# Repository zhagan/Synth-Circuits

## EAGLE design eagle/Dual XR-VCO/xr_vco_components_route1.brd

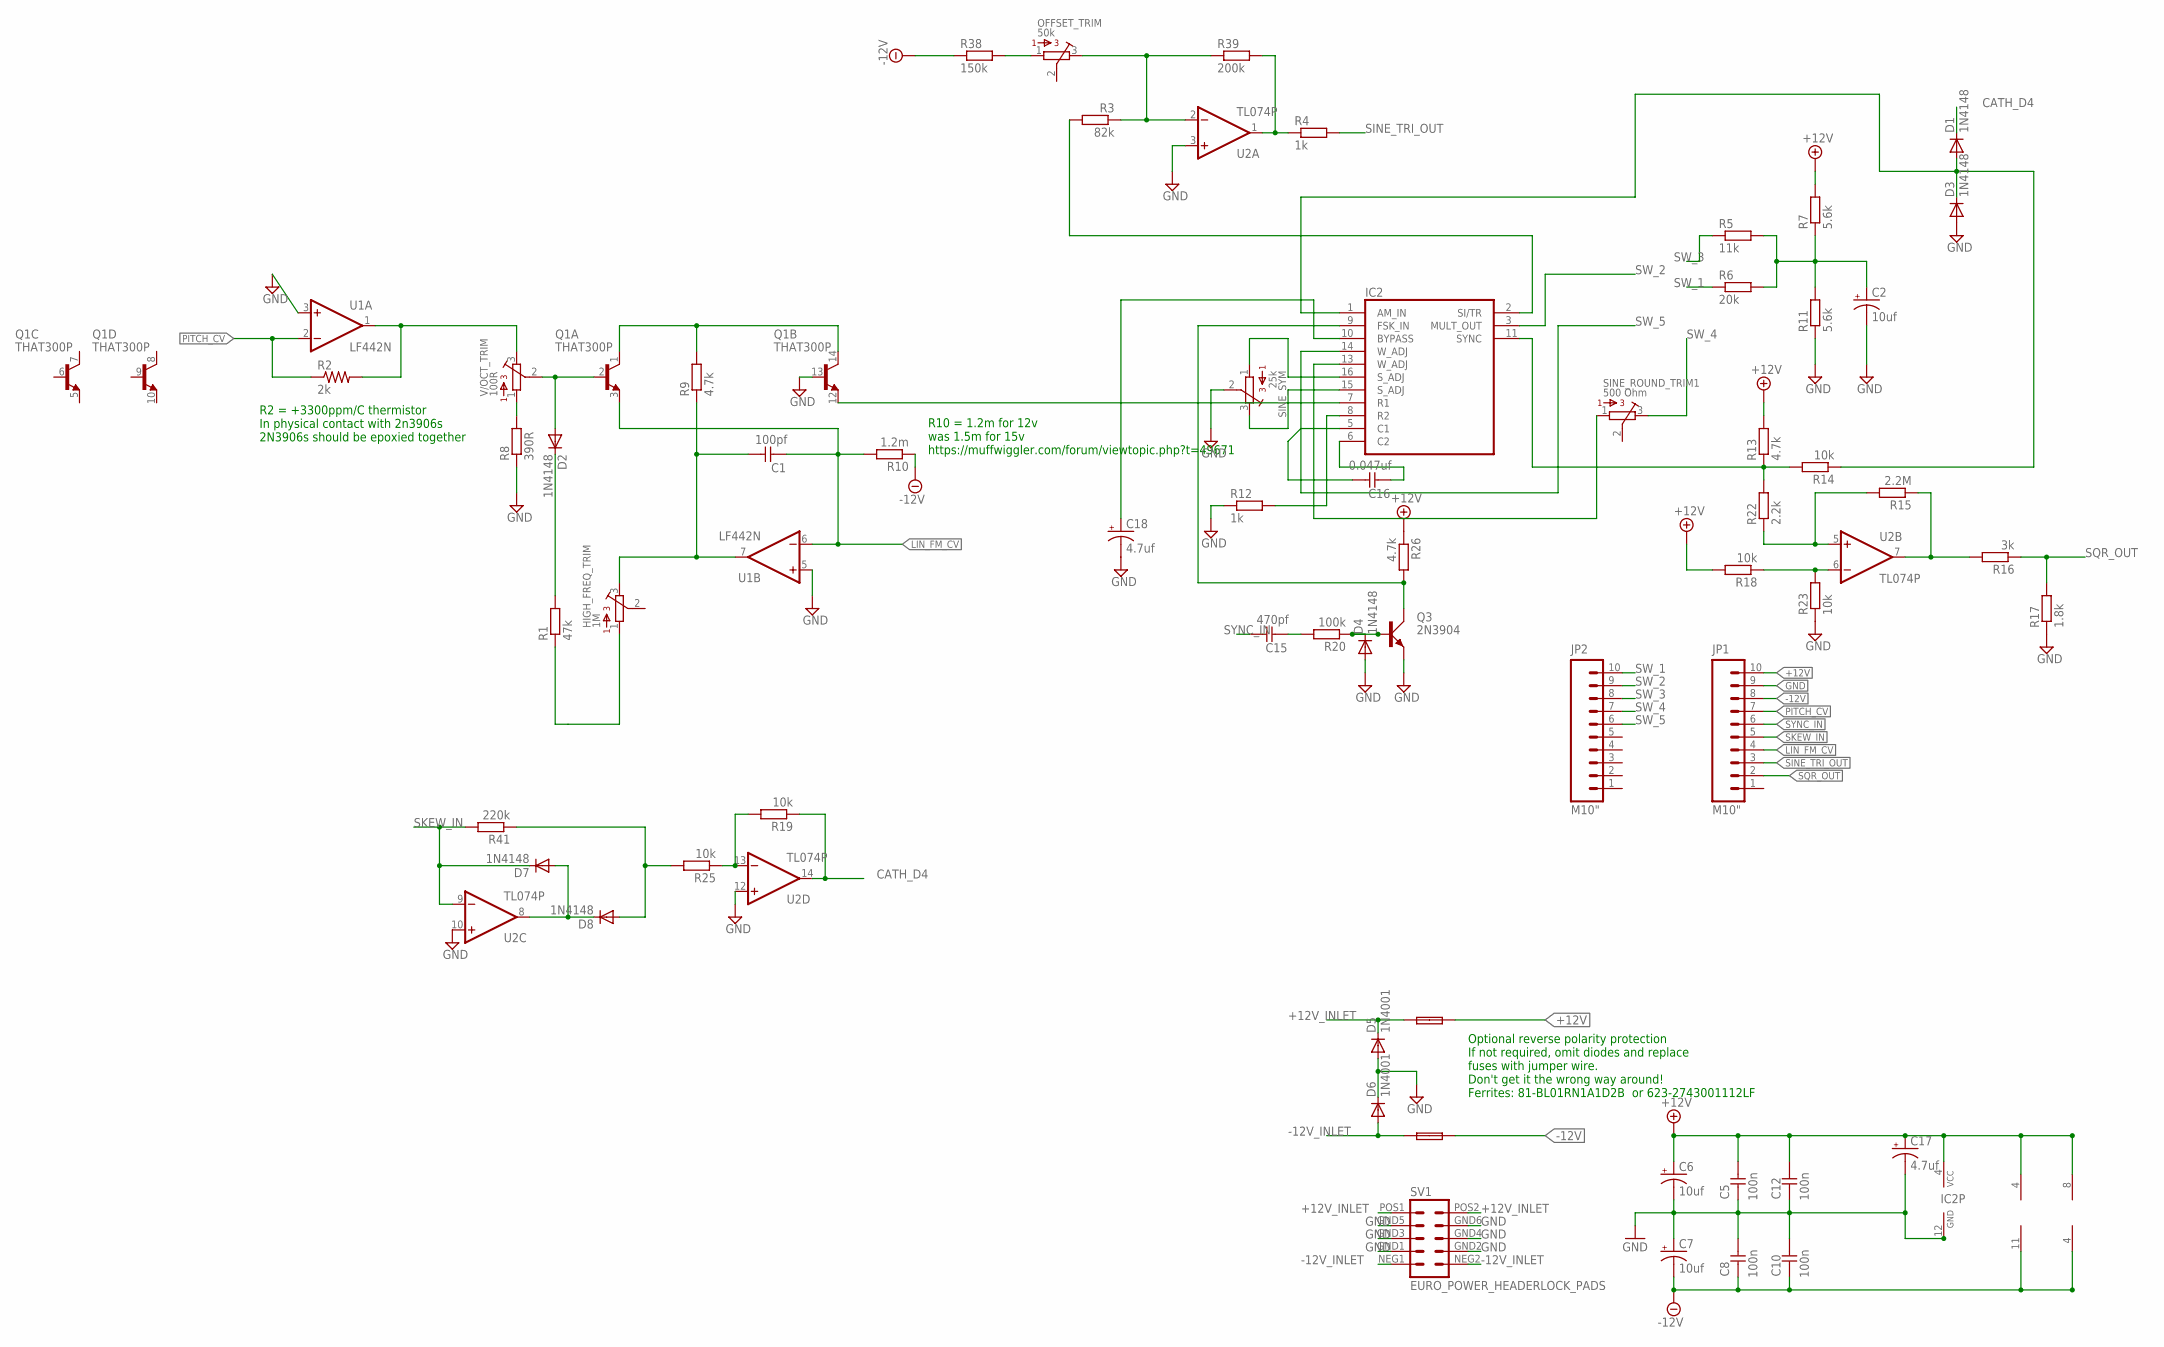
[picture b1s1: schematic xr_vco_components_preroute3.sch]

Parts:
C1: 100pf; C050-024X044
C2, C6, C7: 10uf; CPOL-RADIAL-10UF-25V
C5, C8, C10, C12: 100n; C050-024X044
C15: 470pf; C050-024X044
C16: 0.047uf; C050-024X044
C17, C18: 4.7uf; CPOL-RADIAL-10UF-25V
D1, D2, D3, D4, D7, D8: 1N4148; DO35-7
D5, D6: 1N4001; DO41-10
F1, F2: FUSE; C050H075X075
HIGH_FREQ_TRIM: 1M; BOURNS_3362P_TRIMMER
IC2: XR-2206; DIL16
JP1, JP2: M10"; 1X10
OFFSET_TRIM: 50k; BOURNS_3362P_TRIMMER
Q1: THAT300P; DIL14
Q3: 2N3904; TO92D
R1: 47k; 7MM_RESISTOR
R2: 2k; 0309/12
R3: 82k; 7MM_RESISTOR
R4, R12: 1k; 7MM_RESISTOR
R5: 11k; 7MM_RESISTOR
R6: 20k; 7MM_RESISTOR
R7, R11: 5.6k; 7MM_RESISTOR
R8: 390R; 7MM_RESISTOR
R9, R13, R26: 4.7k; 7MM_RESISTOR
R10: 1.2m; 7MM_RESISTOR
R14, R18, R19, R23, R25: 10k; 7MM_RESISTOR
R15: 2.2M; 7MM_RESISTOR
R16: 3k; 7MM_RESISTOR
R17: 1.8k; 7MM_RESISTOR
R20: 100k; 7MM_RESISTOR
R22: 2.2k; 7MM_RESISTOR
R38: 150k; 7MM_RESISTOR
R39: 200k; 7MM_RESISTOR
R41: 220k; 7MM_RESISTOR
SINE_ROUND_TRIM1: 500 Ohm; BOURNS_3362P_TRIMMER
SINE_SYM: 25k; BOURNS_3362P_TRIMMER
SV1: EURO_POWER_HEADERLOCK_PADS; EURO_PWR_HEADER_LOCK
U1: LF442N; DIL08
U2: TL074P; DIL14
V/OCT_TRIM: 100R; BOURNS_3362P_TRIMMER

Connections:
+12V: C5.1, C6.1 (+), C12.1, C17.1 (+), F1.2, IC2.4 (VCC), JP1.10, R7.2, R13.2, R18.2, R26.1, U1.8 (V+), U2.4 (V+); also elsewhere on the board
+12V_INLET: D5.C, F1.1, SV1.POS1 (10), SV1.POS2 (9)
-12V: C7.2 (-), C8.2, C10.2, F2.2, JP1.8, R10.1, R38.1, U1.4 (V-), U2.11 (V-); also elsewhere on the board
-12V_INLET: D6.A, F2.1, SV1.NEG1 (2), SV1.NEG2 (1)
CATH_D4: D1.C, R19.1, U2.14 (OUT)
GND: C2.2 (-), C5.2, C6.2 (-), C7.1 (+), C8.1, C10.1, C12.2, C17.2 (-), C18.2 (-), D3.A, D4.A, D5.A, D6.C, IC2.12 (GND), JP1.9, Q1.13 (B), Q3.E, R8.1, R11.1, R12.1, R17.1, R23.1, SINE_SYM.2, SV1.GND1 (4), SV1.GND2 (3), SV1.GND3 (6), SV1.GND4 (5), SV1.GND5 (8), SV1.GND6 (7), U1.3 (+IN), U1.5 (+IN), U2.3 (+IN), U2.10 (+IN), U2.12 (+IN); also elsewhere on the board
LIN_FM_CV: C1.2, JP1.4, Q1.3 (E), R10.2, U1.6 (-IN)
unnamed: IC2.7 (R1), Q1.12 (E)
unnamed: D2.C, R1.2
unnamed: HIGH_FREQ_TRIM.1, R1.1
unnamed: IC2.2 (SI/TR), R3.2
unnamed: R2.2, U1.1 (OUT), V/OCT_TRIM.3
unnamed: OFFSET_TRIM.3, R3.1, R39.1, U2.2 (-IN)
unnamed: R8.2, V/OCT_TRIM.1
unnamed: D2.A, Q1.2 (B), V/OCT_TRIM.2
unnamed: Q1.1 (C), Q1.14 (C), R9.2
unnamed: OFFSET_TRIM.1, R38.2
unnamed: R4.1, R39.2, U2.1 (OUT)
unnamed: C1.1, HIGH_FREQ_TRIM.3, R9.1, U1.7 (OUT)
unnamed: C2.1 (+), R5.2, R6.2, R7.1, R11.2
unnamed: IC2.16 (S_ADJ), SINE_SYM.1
unnamed: IC2.13 (W_ADJ), SINE_ROUND_TRIM1.1
unnamed: IC2.15 (S_ADJ), SINE_SYM.3
unnamed: IC2.8 (R2), R12.2
unnamed: R18.1, R23.2, U2.6 (-IN)
unnamed: R15.1, R16.2, U2.7 (OUT)
unnamed: R19.2, R25.1, U2.13 (-IN)
unnamed: R15.2, R22.1, U2.5 (+IN)
unnamed: D1.A, D3.C, IC2.1 (AM_IN), R14.1
unnamed: C15.2, R20.2
unnamed: D4.C, Q3.B, R20.1
unnamed: IC2.11 (SYNC), R13.1, R14.2, R22.2
unnamed: IC2.9 (FSK_IN), Q3.C, R26.2
unnamed: C16.2, IC2.6 (C2)
unnamed: C16.1, IC2.5 (C1)
unnamed: C18.1 (+), IC2.10 (BYPASS)
unnamed: D7.A, D8.C, U2.8 (OUT)
unnamed: D8.A, R25.2, R41.1
PITCH_CV: JP1.7, R2.1, U1.2 (-IN)
SINE_TRI_OUT: JP1.3, R4.2
SKEW_IN: D7.C, JP1.5, R41.2, U2.9 (-IN)
SQR_OUT: JP1.2, R16.1, R17.2
SW_1: JP2.10, R6.1
SW_2: IC2.3 (MULT_OUT), JP2.9
SW_3: JP2.8, R5.1
SW_4: JP2.7, SINE_ROUND_TRIM1.3
SW_5: IC2.14 (W_ADJ), JP2.6
SYNC_IN: C15.1, JP1.6

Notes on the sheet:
R2 = +3300ppm/C thermistor In physical contact with 2n3906s 2N3906s should be epoxied together
R10 = 1.2m for 12v was 1.5m for 15v https://muffwiggler.com/forum/viewtopic.php?t=49671
Optional reverse polarity protection If not required, omit diodes and replace fuses with jumper wire. Don't get it the wrong way around! Ferrites: 81-BL01RN1A1D2B or 623-2743001112LF

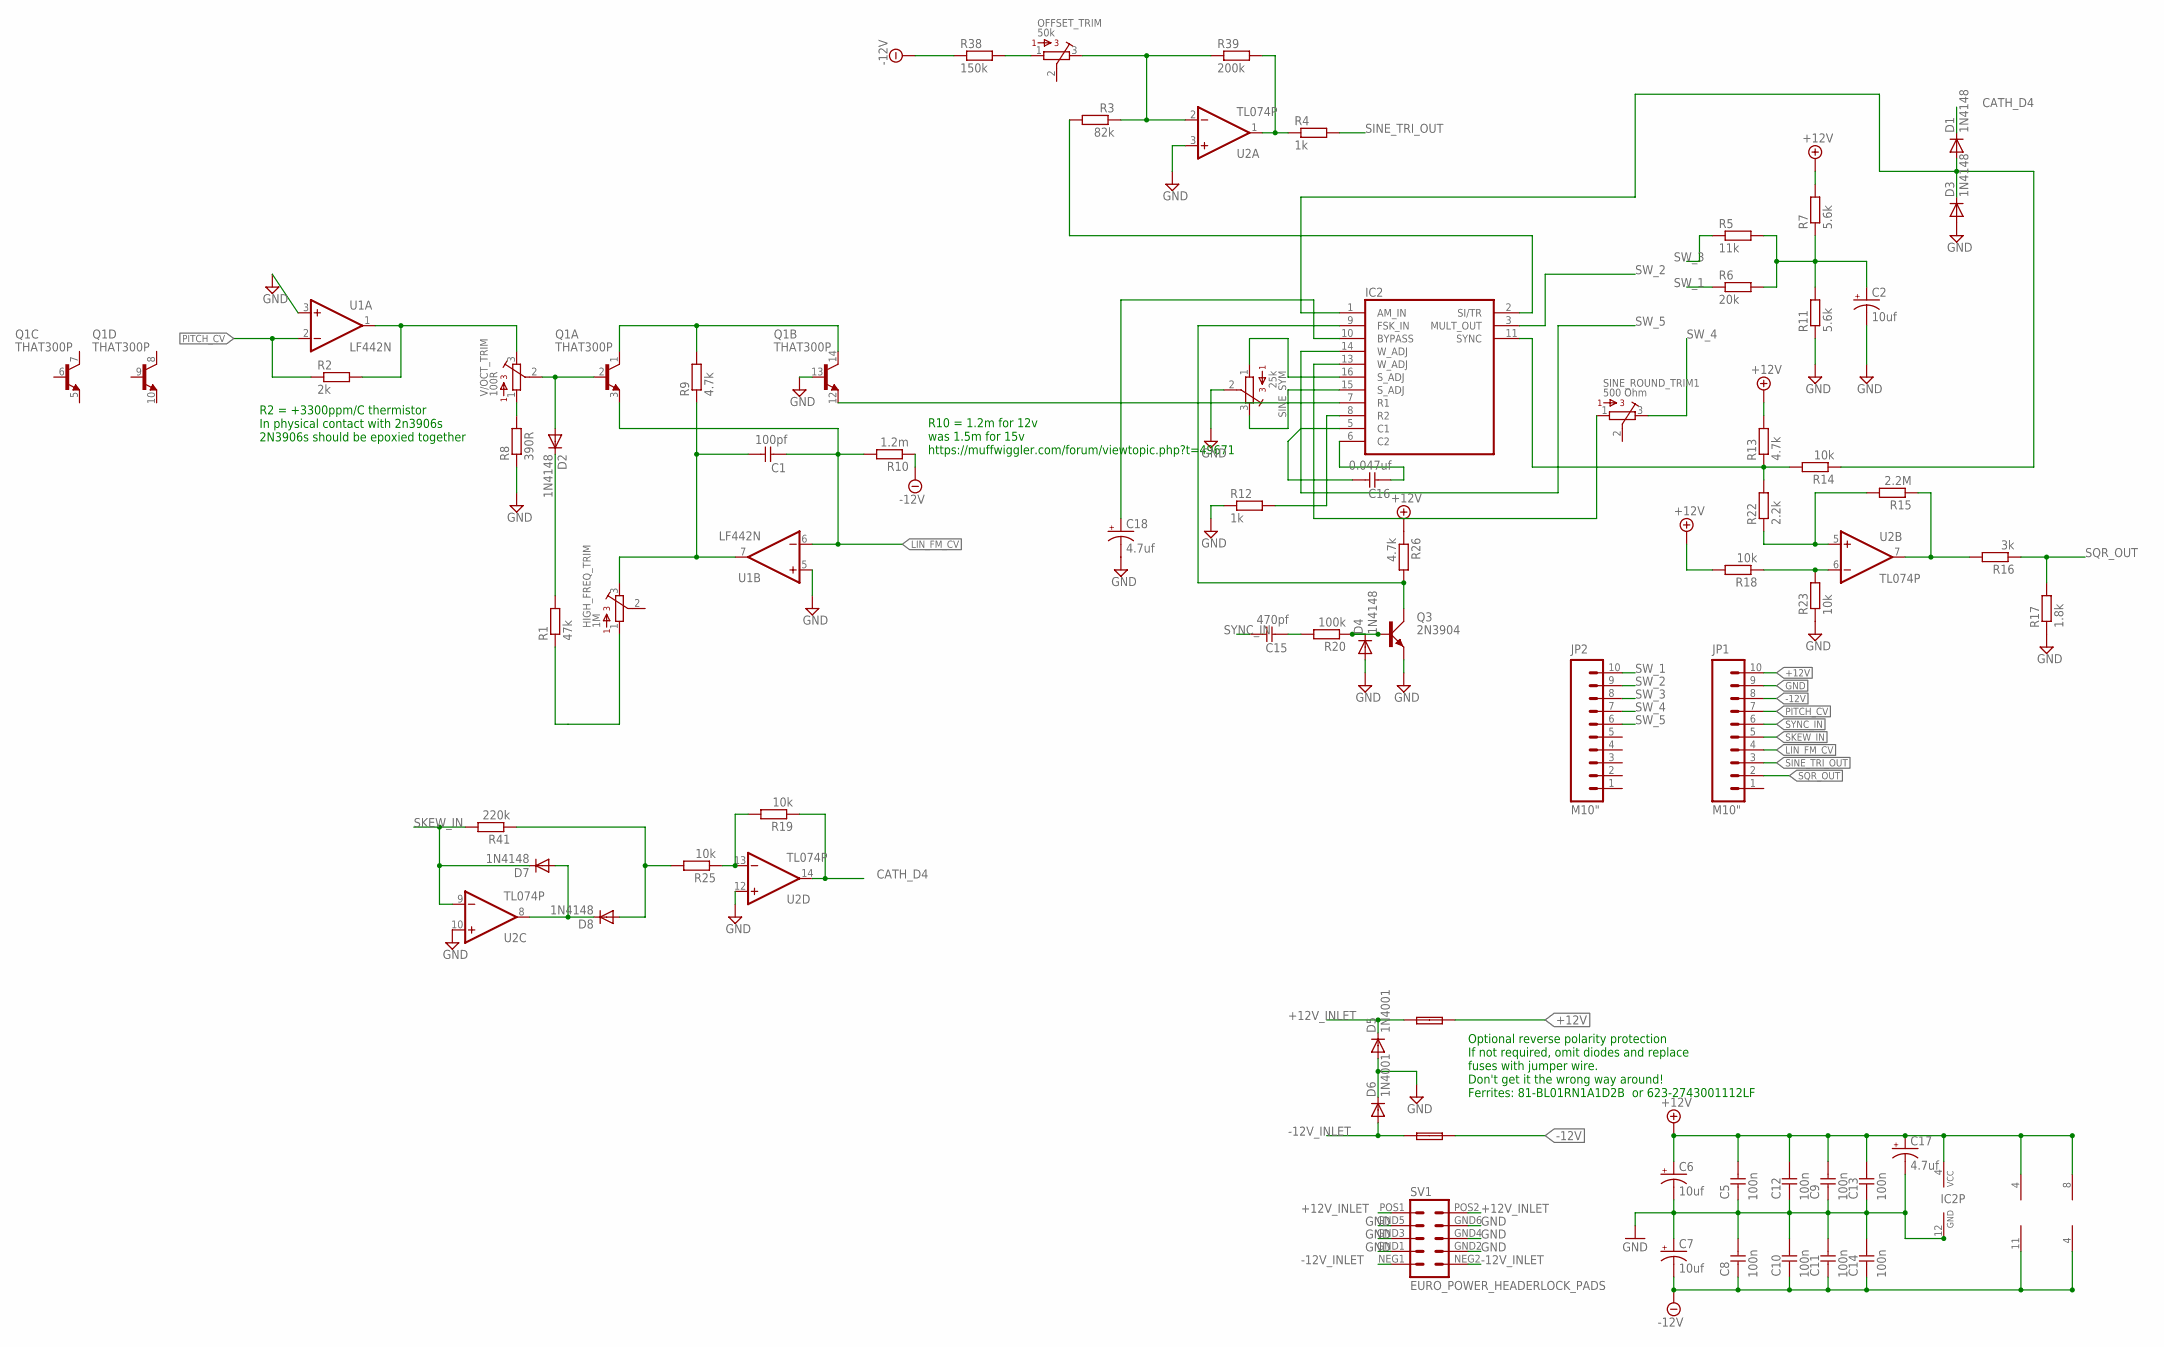
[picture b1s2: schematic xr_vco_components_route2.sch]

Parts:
C1: 100pf; C050-024X044
C2, C6, C7: 10uf; CPOL-RADIAL-10UF-25V
C5, C8, C9, C10, C11, C12, C13, C14: 100n; C050-024X044
C15: 470pf; C050-024X044
C16: 0.047uf; C050-024X044
C17, C18: 4.7uf; CPOL-RADIAL-10UF-25V
D1, D2, D3, D4, D7, D8: 1N4148; DO35-7
D5, D6: 1N4001; DO41-10
F1, F2: FUSE; C050H075X075
HIGH_FREQ_TRIM: 1M; BOURNS_3362P_TRIMMER
IC2: XR-2206; DIL16
JP1, JP2: M10"; 1X10
OFFSET_TRIM: 50k; BOURNS_3362P_TRIMMER
Q1: THAT300P; DIL14
Q3: 2N3904; TO92D
R1: 47k; 7MM_RESISTOR
R2: 2k; 7MM_RESISTOR
R3: 82k; 7MM_RESISTOR
R4, R12: 1k; 7MM_RESISTOR
R5: 11k; 7MM_RESISTOR
R6: 20k; 7MM_RESISTOR
R7, R11: 5.6k; 7MM_RESISTOR
R8: 390R; 7MM_RESISTOR
R9, R13, R26: 4.7k; 7MM_RESISTOR
R10: 1.2m; 7MM_RESISTOR
R14, R18, R19, R23, R25: 10k; 7MM_RESISTOR
R15: 2.2M; 7MM_RESISTOR
R16: 3k; 7MM_RESISTOR
R17: 1.8k; 7MM_RESISTOR
R20: 100k; 7MM_RESISTOR
R22: 2.2k; 7MM_RESISTOR
R38: 150k; 7MM_RESISTOR
R39: 200k; 7MM_RESISTOR
R41: 220k; 7MM_RESISTOR
SINE_ROUND_TRIM1: 500 Ohm; BOURNS_3362P_TRIMMER
SINE_SYM: 25k; BOURNS_3362P_TRIMMER
SV1: EURO_POWER_HEADERLOCK_PADS; EURO_PWR_HEADER_LOCK
U1: LF442N; DIL08
U2: TL074P; DIL14
V/OCT_TRIM: 100R; BOURNS_3362P_TRIMMER

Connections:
+12V: C5.1, C6.1 (+), C9.1, C12.1, C13.1, C17.1 (+), F1.2, IC2.4 (VCC), JP1.10, R7.2, R13.2, R18.2, R26.1, U1.8 (V+), U2.4 (V+)
+12V_INLET: D5.C, F1.1, SV1.POS1 (10), SV1.POS2 (9)
-12V: C7.2 (-), C8.2, C10.2, C11.2, C14.2, F2.2, JP1.8, R10.1, R38.1, U1.4 (V-), U2.11 (V-)
-12V_INLET: D6.A, F2.1, SV1.NEG1 (2), SV1.NEG2 (1)
CATH_D4: D1.C, R19.1, U2.14 (OUT)
GND: C2.2 (-), C5.2, C6.2 (-), C7.1 (+), C8.1, C9.2, C10.1, C11.1, C12.2, C13.2, C14.1, C17.2 (-), C18.2 (-), D3.A, D4.A, D5.A, D6.C, IC2.12 (GND), JP1.9, Q1.13 (B), Q3.E, R8.1, R11.1, R12.1, R17.1, R23.1, SINE_SYM.2, SV1.GND1 (4), SV1.GND2 (3), SV1.GND3 (6), SV1.GND4 (5), SV1.GND5 (8), SV1.GND6 (7), U1.3 (+IN), U1.5 (+IN), U2.3 (+IN), U2.10 (+IN), U2.12 (+IN)
LIN_FM_CV: C1.2, JP1.4, Q1.3 (E), R10.2, U1.6 (-IN)
unnamed: IC2.7 (R1), Q1.12 (E)
unnamed: D2.C, R1.2
unnamed: HIGH_FREQ_TRIM.1, R1.1
unnamed: IC2.2 (SI/TR), R3.2
unnamed: R2.2, U1.1 (OUT), V/OCT_TRIM.3
unnamed: OFFSET_TRIM.3, R3.1, R39.1, U2.2 (-IN)
unnamed: R8.2, V/OCT_TRIM.1
unnamed: D2.A, Q1.2 (B), V/OCT_TRIM.2
unnamed: Q1.1 (C), Q1.14 (C), R9.2
unnamed: OFFSET_TRIM.1, R38.2
unnamed: R4.1, R39.2, U2.1 (OUT)
unnamed: C1.1, HIGH_FREQ_TRIM.3, R9.1, U1.7 (OUT)
unnamed: C2.1 (+), R5.2, R6.2, R7.1, R11.2
unnamed: IC2.16 (S_ADJ), SINE_SYM.1
unnamed: IC2.13 (W_ADJ), SINE_ROUND_TRIM1.1
unnamed: IC2.15 (S_ADJ), SINE_SYM.3
unnamed: IC2.8 (R2), R12.2
unnamed: R18.1, R23.2, U2.6 (-IN)
unnamed: R15.1, R16.2, U2.7 (OUT)
unnamed: R19.2, R25.1, U2.13 (-IN)
unnamed: R15.2, R22.1, U2.5 (+IN)
unnamed: D1.A, D3.C, IC2.1 (AM_IN), R14.1
unnamed: C15.2, R20.2
unnamed: D4.C, Q3.B, R20.1
unnamed: IC2.11 (SYNC), R13.1, R14.2, R22.2
unnamed: IC2.9 (FSK_IN), Q3.C, R26.2
unnamed: C16.2, IC2.6 (C2)
unnamed: C16.1, IC2.5 (C1)
unnamed: C18.1 (+), IC2.10 (BYPASS)
unnamed: D7.A, D8.C, U2.8 (OUT)
unnamed: D8.A, R25.2, R41.1
PITCH_CV: JP1.7, R2.1, U1.2 (-IN)
SINE_TRI_OUT: JP1.3, R4.2
SKEW_IN: D7.C, JP1.5, R41.2, U2.9 (-IN)
SQR_OUT: JP1.2, R16.1, R17.2
SW_1: JP2.10, R6.1
SW_2: IC2.3 (MULT_OUT), JP2.9
SW_3: JP2.8, R5.1
SW_4: JP2.7, SINE_ROUND_TRIM1.3
SW_5: IC2.14 (W_ADJ), JP2.6
SYNC_IN: C15.1, JP1.6

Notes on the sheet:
R2 = +3300ppm/C thermistor In physical contact with 2n3906s 2N3906s should be epoxied together
R10 = 1.2m for 12v was 1.5m for 15v https://muffwiggler.com/forum/viewtopic.php?t=49671
Optional reverse polarity protection If not required, omit diodes and replace fuses with jumper wire. Don't get it the wrong way around! Ferrites: 81-BL01RN1A1D2B or 623-2743001112LF

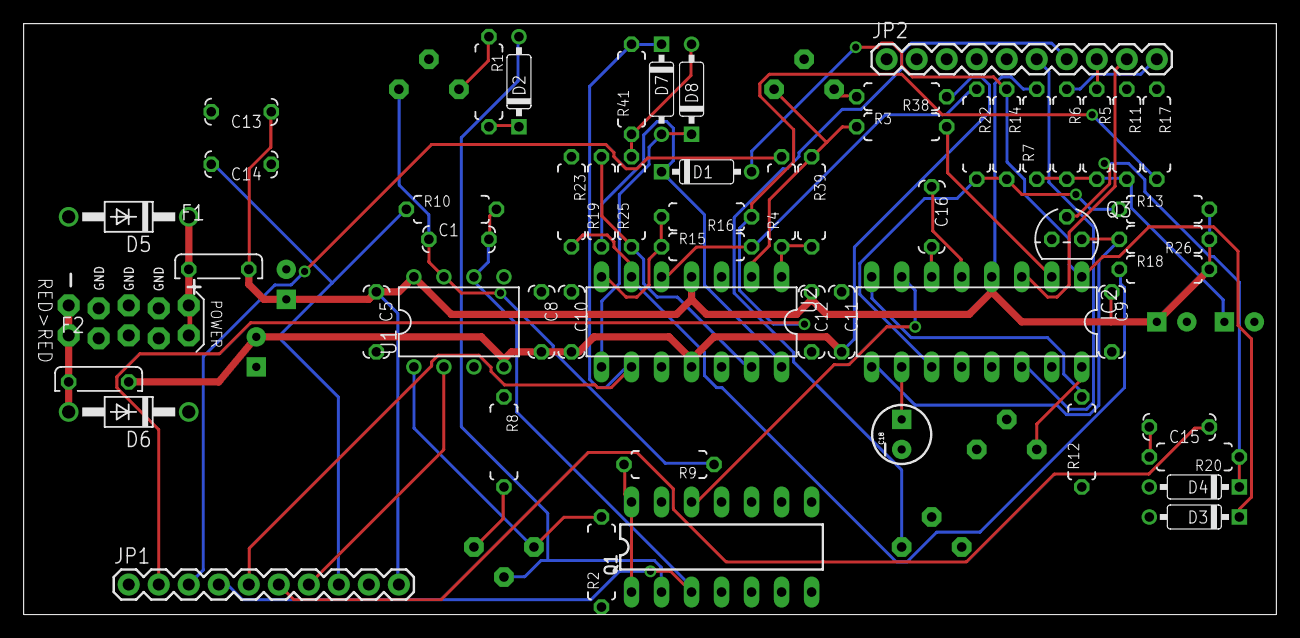
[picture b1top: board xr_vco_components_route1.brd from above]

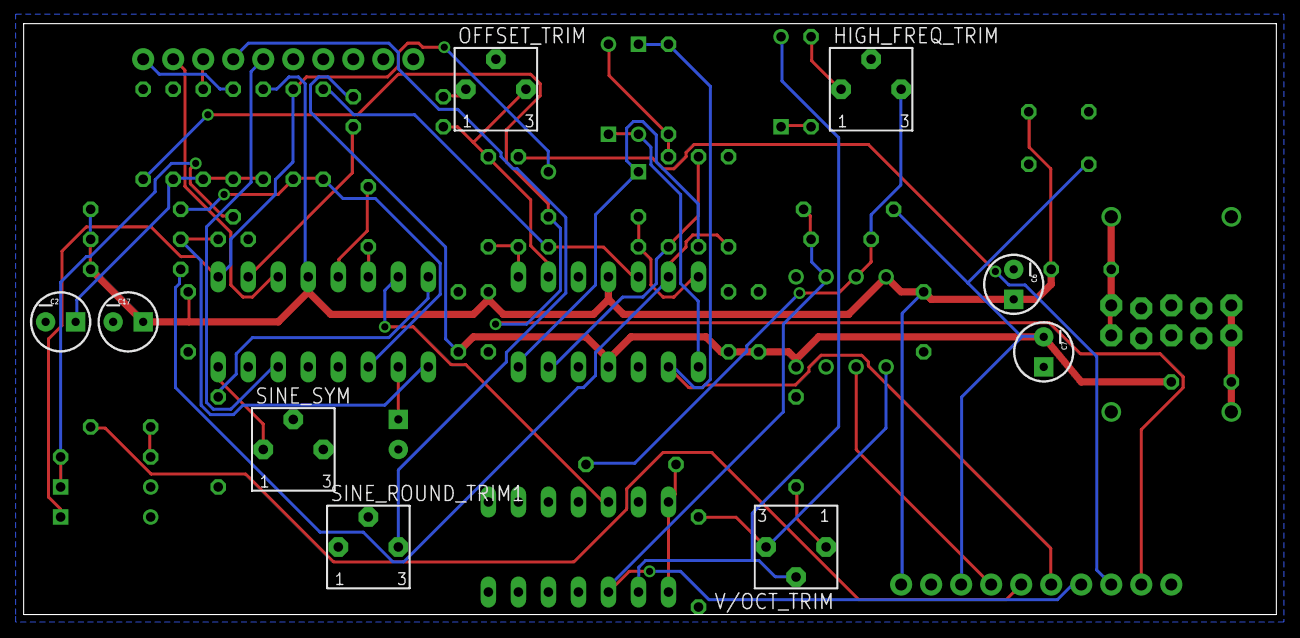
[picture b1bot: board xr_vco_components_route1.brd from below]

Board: 2 copper layers, 106.0 x 50.0 mm, 66 parts (9 on the bottom side), 48 nets.

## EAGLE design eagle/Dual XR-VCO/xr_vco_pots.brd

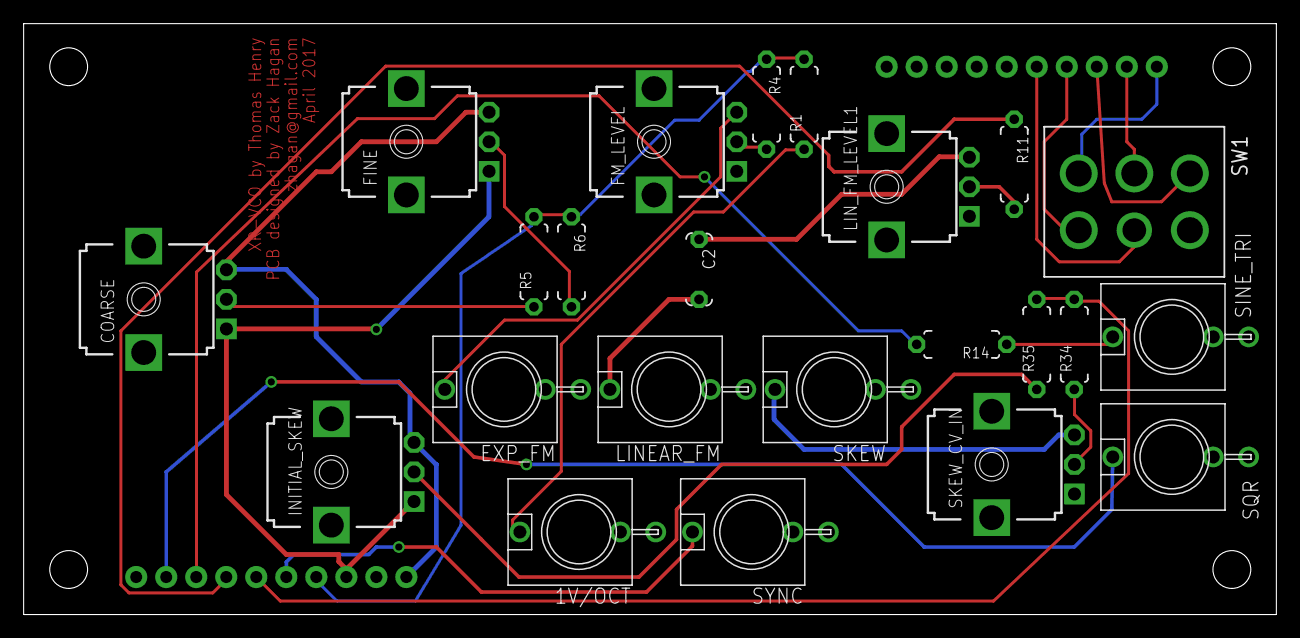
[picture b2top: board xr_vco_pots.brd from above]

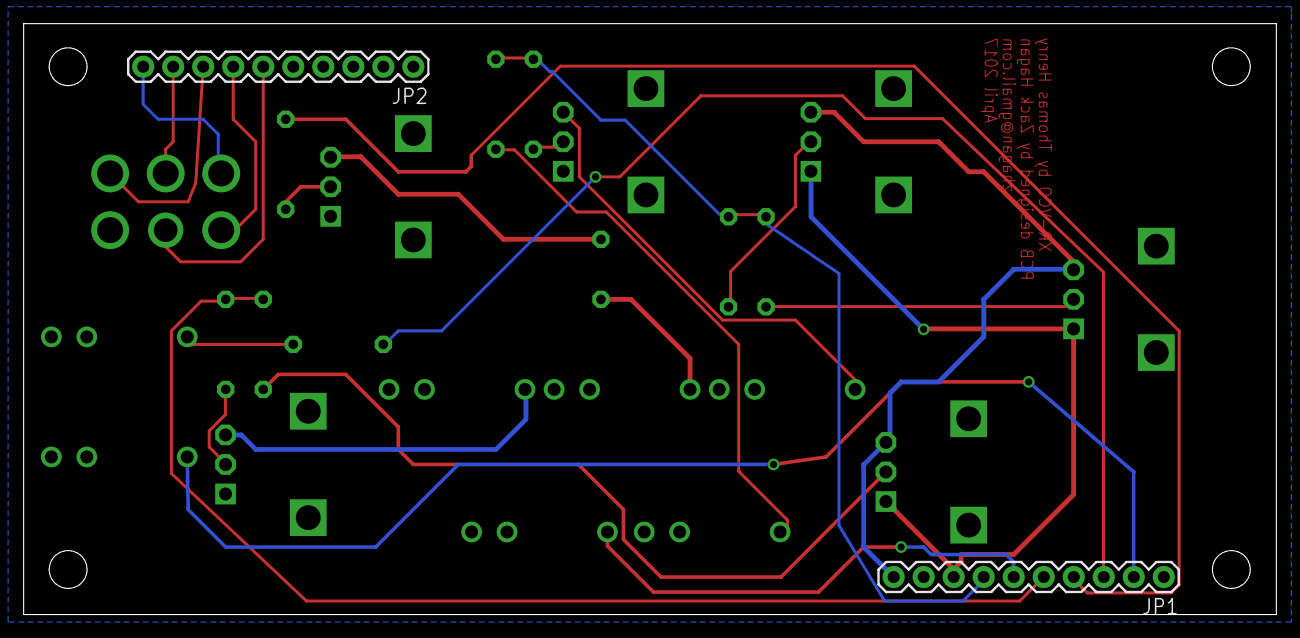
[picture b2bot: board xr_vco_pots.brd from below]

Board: 2 copper layers, 106.0 x 50.0 mm, 29 parts (2 on the bottom side), 26 nets.

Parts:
1V/OCT: THONKICONNNEW; WQP-PJ301M-12_JACK
C2: 220nf; C050-024X044
COARSE: 100k; 9MM_SNAP-IN_POT
EXP_FM: THONKICONNNEW; WQP-PJ301M-12_JACK
FINE: 100k; 9MM_SNAP-IN_POT
FM_LEVEL: 100k; 9MM_SNAP-IN_POT
INITIAL_SKEW: 100k; 9MM_SNAP-IN_POT
JP1, JP2: M10"; 1X10
LINEAR_FM: THONKICONNNEW; WQP-PJ301M-12_JACK
LIN_FM_LEVEL1: 100k; 9MM_SNAP-IN_POT
R1, R4, R5, R11, R34: 100k; 7MM_RESISTOR
R6: 2.4M; 7MM_RESISTOR
R14: 1k; 7MM_RESISTOR
R35: 330k; 7MM_RESISTOR
SINE_TRI: THONKICONNNEW; WQP-PJ301M-12_JACK
SKEW: THONKICONNNEW; WQP-PJ301M-12_JACK
SKEW_CV_IN: 100k; 9MM_SNAP-IN_POT
SQR: THONKICONNNEW; WQP-PJ301M-12_JACK
SW1: DPDT
SYNC: THONKICONNNEW; WQP-PJ301M-12_JACK
U$1, U$2, U$3, U$4: MOUNTING_HOLE

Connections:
+12V: COARSE.3, FINE.3, INITIAL_SKEW.3, JP1.10
-12V: COARSE.1, FINE.1, INITIAL_SKEW.1, JP1.8
GND: 1V/OCT.P$3_SLEEVE, COARSE.CHASSIS2, EXP_FM.P$3_SLEEVE, FINE.CHASSIS2, FM_LEVEL.1, FM_LEVEL.CHASSIS2, INITIAL_SKEW.CHASSIS2, JP1.9, LINEAR_FM.P$3_SLEEVE, LIN_FM_LEVEL1.1, LIN_FM_LEVEL1.CHASSIS2, SINE_TRI.P$3_SLEEVE, SKEW.P$3_SLEEVE, SKEW_CV_IN.1, SKEW_CV_IN.CHASSIS2, SQR.P$3_SLEEVE, SYNC.P$3_SLEEVE
LIN_FM_CV: JP1.4, R11.1
unnamed: 1V/OCT.P$1_TIP, R1.1
unnamed: EXP_FM.P$1_TIP, FM_LEVEL.3
unnamed: FM_LEVEL.2, R4.2
unnamed: COARSE.2, R5.1
unnamed: FINE.2, R6.2
unnamed: LIN_FM_LEVEL1.2, R11.2
unnamed: R14.1, SINE_TRI.P$1_TIP
unnamed: C2.1, LIN_FM_LEVEL1.3
unnamed: C2.2, LINEAR_FM.P$1_TIP
unnamed: SKEW.P$1_TIP, SKEW_CV_IN.3
unnamed: R34.1, SKEW_CV_IN.2
unnamed: INITIAL_SKEW.2, R35.1
PITCH_CV: JP1.7, R1.2, R4.1, R5.2, R6.1
SINE_TRI_OUT: JP1.3, R14.2
SKEW_IN: JP1.5, R34.2, R35.2
SQR_OUT: JP1.2, SQR.P$1_TIP
SW_1: JP2.10, SW1.A3
SW_2: JP2.9, SW1.A2
SW_3: JP2.8, SW1.A1
SW_4: JP2.7, SW1.B3
SW_5: JP2.6, SW1.B2
SYNC_IN: JP1.6, SYNC.P$1_TIP

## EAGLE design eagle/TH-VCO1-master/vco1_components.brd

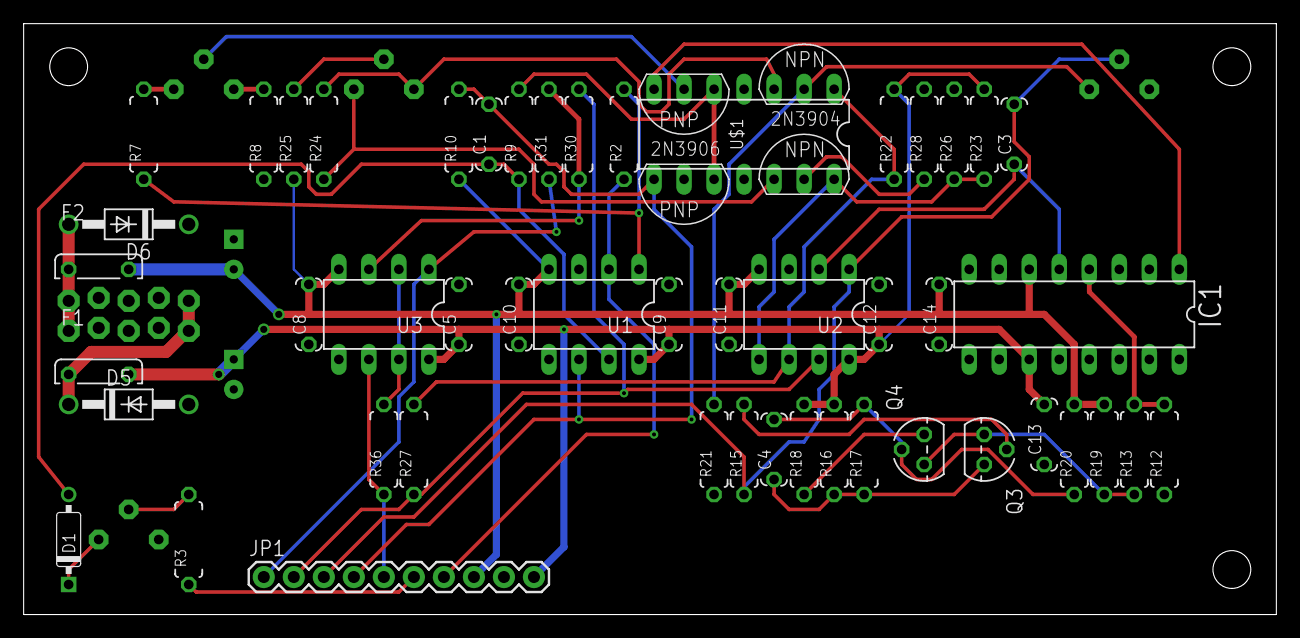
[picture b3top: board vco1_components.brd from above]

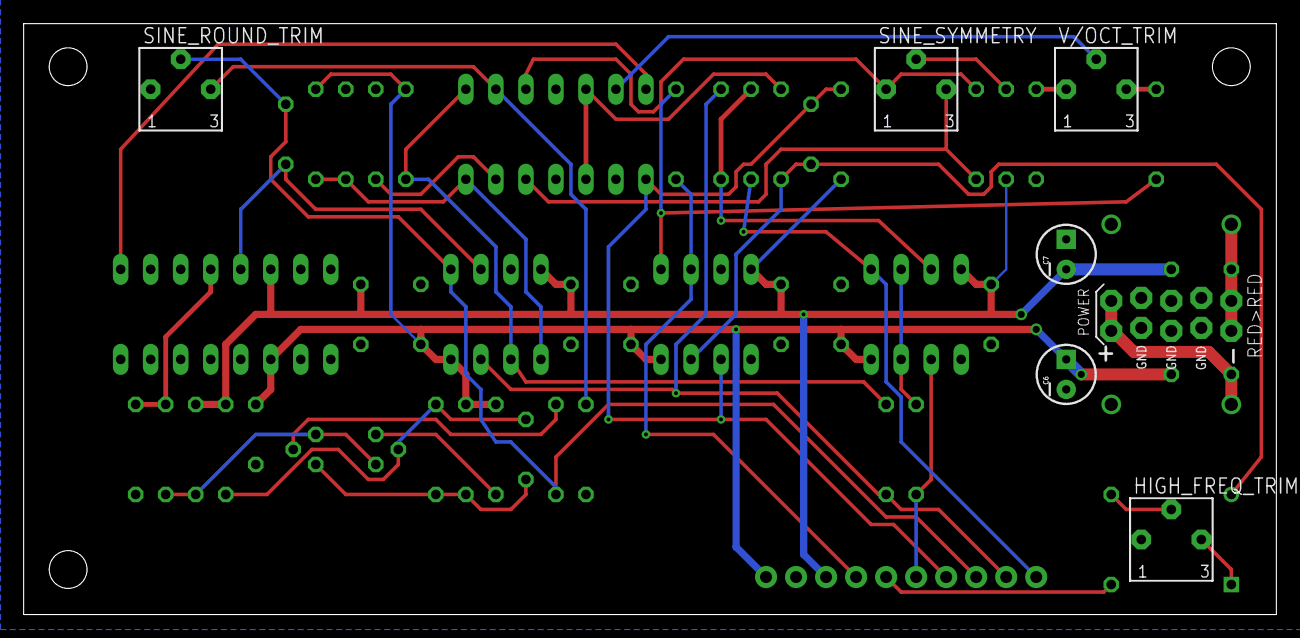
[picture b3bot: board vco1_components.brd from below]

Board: 4 copper layers, 106.0 x 50.0 mm, 59 parts (7 on the bottom side), 37 nets.

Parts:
C1, C3: 1nf; C050-024X044
C4: 47pf; C050-024X044
C5, C8, C9, C10, C11, C12, C13, C14: 100n; C050-024X044
C6, C7: 10uf; CPOL-RADIAL-10UF-25V
D1: 1N4148; DO35-7
D5, D6: 1N4001; DO41-10
F1, F2: FUSE; C050H075X075
HIGH_FREQ_TRIM: 100k; BOURNS_3362P_TRIMMER
IC1: LM13700N; DIL16
JP1: M10"; 1X10
Q3, Q4: 2N3904; TO92D
R2: 2k; 7MM_RESISTOR
R3, R31: 2.2m; 7MM_RESISTOR
R7: 47R; 7MM_RESISTOR
R8: 820R; 7MM_RESISTOR
R9: 22k; 7MM_RESISTOR
R10: 1.2m; 7MM_RESISTOR
R12, R19, R22, R23: 10k; 7MM_RESISTOR
R13, R20: 100k; 7MM_RESISTOR
R15: 27k; 7MM_RESISTOR
R16: 20k; 7MM_RESISTOR
R17, R25: 18k; 7MM_RESISTOR
R18: 5.1k; 7MM_RESISTOR
R21, R28, R30: 2.2k; 7MM_RESISTOR
R24: 390R; 7MM_RESISTOR
R26, R27: 12k; 7MM_RESISTOR
R36: 150k; 7MM_RESISTOR
SINE_ROUND_TRIM: 100k; BOURNS_3362P_TRIMMER
SINE_SYMMETRY: 50k; BOURNS_3362P_TRIMMER
SV1: EURO_POWER_HEADERLOCK_PADS; EURO_PWR_HEADER_LOCK
U1, U2, U3: TL072_; DIL08
U$1: THAT-340TRANSISTORS; THAT340
U$2, U$3, U$4: MOUNTING_HOLE
V/OCT_TRIM: 100R; BOURNS_3362P_TRIMMER

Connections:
+12V: C5.1, C6.1, C9.1, C12.1, C13.2, F1.2, IC1.11, JP1.10, R16.2, R18.2, R22.2, R23.2, U1.8, U2.8, U3.8
+12V_INLET: D5.C, F1.1, SV1.POS1, SV1.POS2
-12V: C7.2, C8.2, C10.2, C11.2, C14.2, F2.2, IC1.6, JP1.8, R10.1, R19.2, R20.2, R25.1, U1.4, U2.4, U3.4
-12V_INLET: D6.A, F2.1, SV1.NEG1, SV1.NEG2
CV_A: JP1.7, R2.1, U1.2
CV_B: JP1.6, R3.1
GND: C5.2, C6.2, C7.1, C8.1, C9.2, C10.1, C11.1, C12.2, C13.1, C14.1, D5.A, D6.C, HIGH_FREQ_TRIM.1, IC1.3, IC1.7, IC1.10, JP1.9, R8.1, R12.1, R21.1, R26.2, R28.2, SV1.GND1, SV1.GND2, SV1.GND3, SV1.GND4, SV1.GND5, SV1.GND6, U1.3, U1.5, U2.3, U3.5, U$1.9
LIN_FM_CV: C1.2, JP1.4, R10.2, U1.6, U$1.8
unnamed: R2.2, R7.1, U1.1
unnamed: R7.2, V/OCT_TRIM.3
unnamed: R8.2, V/OCT_TRIM.1
unnamed: U$1.6, V/OCT_TRIM.2
unnamed: R9.2, U$1.5, U$1.10
unnamed: IC1.1, U$1.7
unnamed: C1.1, D1.A, R9.1, U1.7
unnamed: D1.C, HIGH_FREQ_TRIM.3
unnamed: HIGH_FREQ_TRIM.2, R3.2
unnamed: IC1.4, R12.2, R13.2
unnamed: C3.1, IC1.5, U2.2
unnamed: Q3.B, R15.2
unnamed: C4.1, Q3.C, R16.1, R17.1
unnamed: R21.2, SINE_ROUND_TRIM.3, U$1.2
unnamed: C4.2, Q4.B, R17.2, R20.1
unnamed: Q4.C, R18.1
unnamed: R25.2, SINE_SYMMETRY.2
unnamed: Q3.E, Q4.E, R13.1, R19.1
unnamed: R22.1, R27.2, U2.6, U$1.1
unnamed: R23.1, R26.1, U2.5, U$1.14
unnamed: R24.2, SINE_SYMMETRY.1, U$1.3
unnamed: R24.1, SINE_SYMMETRY.3, U$1.12
unnamed: R28.1, U$1.13
unnamed: R30.1, R31.2, U3.3
unnamed: R36.2, U3.2, U3.7
PWM_CV: JP1.5, R36.1, U3.6
PW_OUT: JP1.1, R31.1, U3.1
SIN_OUT: JP1.2, R27.1, R30.2, U2.7
TRI_OUT: C3.2, JP1.3, R15.1, SINE_ROUND_TRIM.2, U2.1

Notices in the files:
parts and their libraries:
SparkFun-Passives: Licensing: CC v3.0 Share-Alike You are welcome to use this library for commercial purposes.
that-corp: Copyright (C) 2008-2010, Bob Starr
